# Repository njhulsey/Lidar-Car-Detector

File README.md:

# Lidar-Car-Detector
Senior year, I applied for an entrepreneurship class where I would develop and idea over the course of a school year. I decided to use my skills in engineering to help cyclists with "bike lash." Over the course of the school I researched and developed my idea into a working prototype. I created a sensor that would fit on the back of a cyclist's bike and notify them as a car approached from behind.

THINGS I LEARNED:
- Public speeking
- Presenting for money
- Fleshing out an idea and brainstorming
- How to use LIDAR Lite 3
- Programming ATTINY45's and how to use them with the sensor.

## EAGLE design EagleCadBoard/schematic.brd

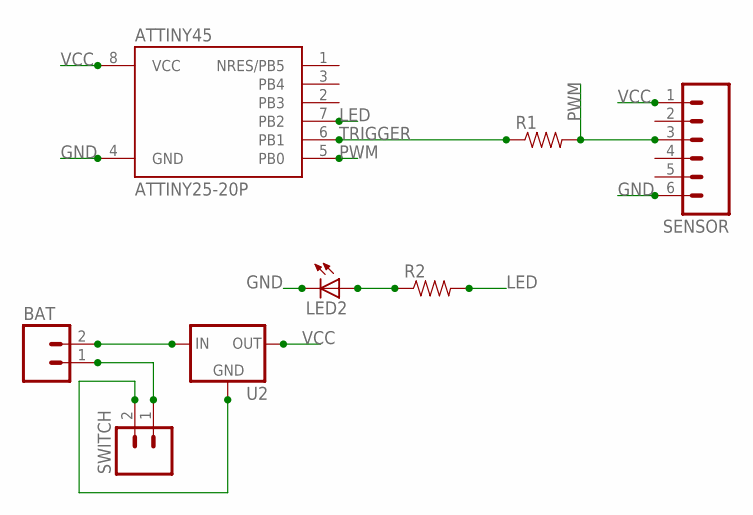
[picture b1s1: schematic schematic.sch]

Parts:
ATTINY45: ATTINY25-20P; PDIP08_300MIL
BAT: M02PTH; 1X02
LED2: LED3MM
R1, R2: 10KOHM-1/6W-5%(PTH)KIT; AXIAL-0.3-KIT
SENSOR: M06NO_SILK_FEMALE_PTH; 1X06_NO_SILK
SWITCH: M02PTH; 1X02
U2: V_REG_78XX-TO-220; TO-220-ALT

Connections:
GND: ATTINY45.4 (GND), LED2.K (C), SENSOR.6, SWITCH.2, U2.GND
LED: ATTINY45.7 (PB2), R2.P$2 (2)
unnamed: BAT.1, SWITCH.1
unnamed: LED2.A, R2.P$1 (1)
PWM: ATTINY45.5 (PB0), R1.P$2 (2), SENSOR.3
SWITCHOUT: BAT.2, U2.IN
TRIGGER: ATTINY45.6 (PB1), R1.P$1 (1)
VCC: ATTINY45.8 (VCC), SENSOR.1, U2.OUT

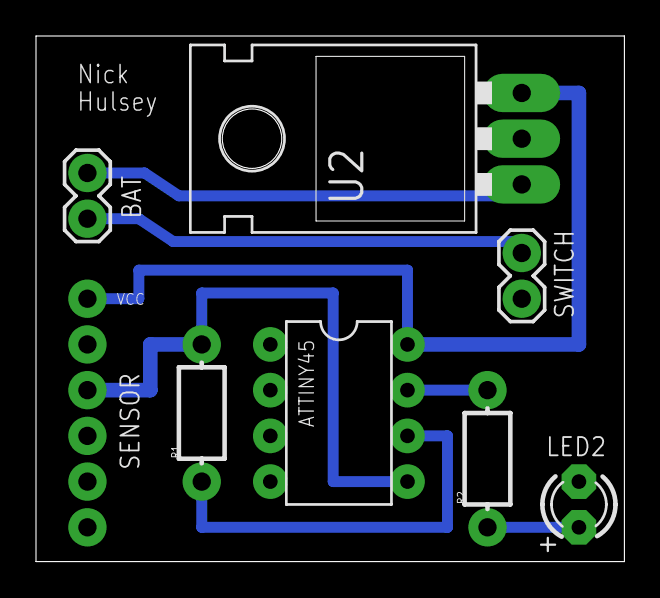
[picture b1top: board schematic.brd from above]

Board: 2 copper layers, 32.7 x 29.2 mm, 8 parts (0 on the bottom side), 8 nets.

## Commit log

2018-03-11 Create init

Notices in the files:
parts and their libraries:
SparkFun-PowerIC: Licensing: Creative Commons ShareAlike 4.0 International - https://creativecommons.org/licenses/by-sa/4.0
